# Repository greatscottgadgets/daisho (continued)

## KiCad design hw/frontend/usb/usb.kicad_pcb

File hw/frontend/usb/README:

Copyright (c) 2014 Jared Boone, ShareBrained Technology, Inc.

These files are part of Daisho.

License
=======

This is a free hardware design; you can redistribute it and/or modify
it under the terms of the GNU General Public License as published by
the Free Software Foundation; either version 2, or (at your option)
any later version.

This design is distributed in the hope that it will be useful,
but WITHOUT ANY WARRANTY; without even the implied warranty of
MERCHANTABILITY or FITNESS FOR A PARTICULAR PURPOSE.  See the
GNU General Public License for more details.

You should have received a copy of the GNU General Public License
along with this design; see the file COPYING.  If not, write to
the Free Software Foundation, Inc., 51 Franklin Street,
Boston, MA 02110-1301, USA.

Hardware Notes
==============

Schematic and layout files were designed in KiCad (release 2014-09-15
bzr 5135 -product), an open source electronic design automation package.

Order and type of copper layers:
    1_top: signal, front ("component" side, where most components are mounted)
    2: ground plane
    3: signal
    4: signal
    5: ground plane
    6_bot: signal, back (a few components mounted, mostly small passives)

PCB description:

    6 layer PCB, 62 mil +/- 5% thickness, using 8 layer construction

    LPI mask          0.4 mil
    Plating           1.2 mil   1.0 oz
    Copper      1     0.7 mil   0.5 oz
    Dielectric  1-2   4.4 mil   prepreg, 2 x 106-FR4 370
    Copper      2     1.2 mil   1.0 oz
    Dielectric  2-3   6.0 mil   core, FR4 370
    Copper      3     1.2 mil   1.0 oz
    Dielectric  3-4   8.1 mil   prepreg, 3 x 1080-FR4 370
                3-4  14.5 mil   core, FR4 370
                3-4   8.1 mil   prepreg, 3 x 1080-FR4 370
    Copper      4     1.2 mil   1.0 oz
    Dielectric  4-5   6.0 mil   core, FR4 370
    Copper      5     1.2 mil   1.0 oz
    Dielectric  5-6   4.4 mil   prepreg, 2 x 106-FR4 370
    Copper      6     0.7 mil   0.5 oz
    Plating           1.2 mil   1.0 oz
    LPI mask          0.4 mil

Impedance Goals
===============

50 Ohm +/- 10% microstrip, layers 1:2 and 6:5 at 0.178 mm (7.0 mil) width

50 Ohm +/- 10% offset stripline, layers 3:2 and 4:5 at 0.165 mm (6.5 mil) width

90 Ohm +/- 10% differential microstrip, layers 1:2 and 6:5 at 0.127 mm (5.0 mil) width, 0.127 mm (5.0 mil) separation

Soldermask
==========

Double side solder mask green
    +/- 5 mil solder mask registration

Silkscreen
==========

Double side silkscreen white
    6 mil silkscreen minimum width
    Silkscreen must be clipped by soldermask

Traces
======

5 mil (0.127 mm) min trace width
5 mil (0.127 mm) min trace isolation

Vias
====

8 mil (0.2032 mm) min via drill
17.7 mil (0.45 mm) min via pad
    4.85 mil min annular ring

Via-in-pad used in many places

Vias in pads need to be filled for assembly
    Most (all?) vias in pads are in capacitor footprints near the two 175-BGAs

Drills
======

Drills are specified in two files:
    usb_drill.xln contains plated drills.
    usb_drill_npth.xln contains non-plated drills.

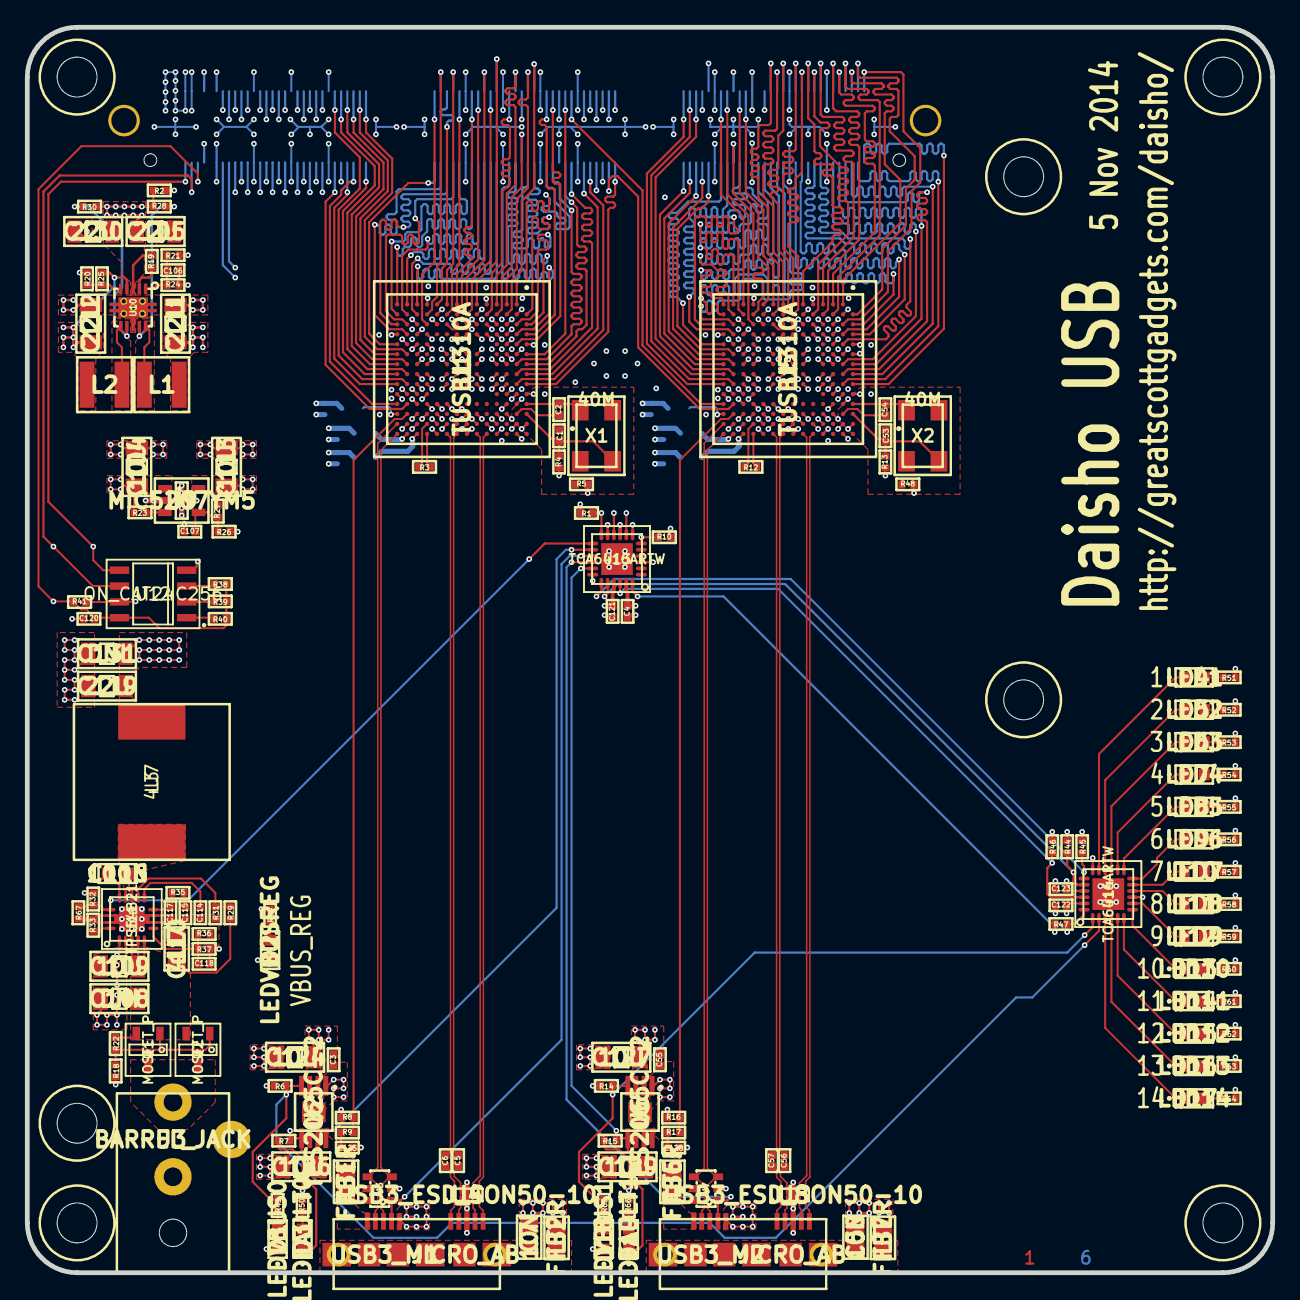
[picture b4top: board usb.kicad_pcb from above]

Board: 6 copper layers, 100.0 x 100.0 mm, 261 parts (0 on the bottom side), 265 nets.

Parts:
C1, C2, C53, C54: 27P; IPC_CAPC1005X55N
C3, C4, C5, C6, C8, C9, C10, C11, C12, C13, C14, C15, C16, C17, C18, C19, C20, C21, C22, C23, C24, C25, C26, C27, C28, C29, C30, C31, C32, C33, C34, C35, C36, C37, C38, C40, C41, C42, C43, C44, C45, C46, C47, C48, C49, C50, C51, C52, C55, C56, C57, C59, C60, C61, C62, C63, C64, C65, C66, C67, C68, C69, C70, C71, C72, C73, C74, C75, C76, C77, C78, C79, C80, C81, C82, C83, C84, C85, C86, C87, C88, C89, C91, C92, C93, C94, C95, C96, C97, C98, C99, C100, C101, C102, C103, C120, C121, C122, C123, C125, C128: 100N; IPC_CAPC1005X55N
C7, C58: 10N; IPC_CAPC2012X140N
C39, C90: 1U; IPC_CAPC1005X55N
C104, C109, C113, C124, C126, C127, C129: 10U; IPC_CAPC3216X180N
C105, C111, C112, C119, C130: 22U; IPC_CAPC3216X180N
C106: 33P; IPC_CAPC1005X55N
C107: 470P; IPC_CAPC1005X55N
C108, C131: DNI; IPC_CAPC3216X180N
C110: 4U7; IPC_CAPC2012X140N
C114: 22N; IPC_CAPC1005X55N
C115: 82N; IPC_CAPC1005X55N
C116: 100N; IPC_CAPC1608X90N
C117: 1N5; IPC_CAPC1005X55N
C118: 220P; IPC_CAPC1005X55N
D1: LEDVBUS0; IPC_LEDC1608X60N
D2: LEDVBUSREG; IPC_LEDC1608X60N
D3: LEDFAULT0; IPC_LEDC1608X60N
D4: LED1; IPC_LEDC1608X60N
D5: LED2; IPC_LEDC1608X60N
D6: LED3; IPC_LEDC1608X60N
D7: LED4; IPC_LEDC1608X60N
D8: LED5; IPC_LEDC1608X60N
D9: LED6; IPC_LEDC1608X60N
D10: LED7; IPC_LEDC1608X60N
D11: LED8; IPC_LEDC1608X60N
D12: LED9; IPC_LEDC1608X60N
D13: LED10; IPC_LEDC1608X60N
D14: LED11; IPC_LEDC1608X60N
D15: LED12; IPC_LEDC1608X60N
D16: LED13; IPC_LEDC1608X60N
D17: LED14; IPC_LEDC1608X60N
D18: LEDVBUS1; IPC_LEDC1608X60N
D19: LEDFAULT1; IPC_LEDC1608X60N
FB1, FB2, FB3, FB4, FB5, FB6, FB7, FB8, FB9, FB10: FILTER; IPC_INDC2012X130N
H1, H2, H4, H5, H6, H7, H8: HOLE; GSG-HOLE126MIL
J1, J2: USB3_MICRO_AB
J3: BARREL_JACK; CUI_PJ-102[AB]H
J4: SAMTEC_QSH-090-D; SAMTEC_QSH-090-01-F-D-A
L1, L2: 4U7; GSG-NRG4026
L3: 4U7; BOURNS_SRR1260
P4, P5, P6, P7, P8: CONN_1; GSG-TESTPOINT-50MIL
Q1, Q2: MOSFET_P; IPC_SOT95P280X125-3N_GSD
R1, R2, R3, R6, R7, R8, R10, R12, R14, R15, R16, R19, R44, R45, R46, R47: 10K; IPC_RESC1005X40N
R4, R5, R13, R38, R39, R40, R41, R48: DNI; IPC_RESC1005X40N
R9, R17: 90K9; IPC_RESC1005X40N
R18, R22: 30K; IPC_RESC1005X40N
R20: 165K; IPC_RESC1005X40N
R21: 180K; IPC_RESC1005X40N
R23, R28, R30: 0R; IPC_RESC1005X40N
R24: 360K; IPC_RESC1005X40N
R25: 137K; IPC_RESC1005X40N
R26: 174K; IPC_RESC1005X40N
R27: 105K; IPC_RESC1005X40N
R29: 22K; IPC_RESC1005X40N
R31: 9K53; IPC_RESC1005X40N
R32: 49K9; IPC_RESC1005X40N
R33: 52K3; IPC_RESC1005X40N
R34, R49, R50, R51, R52, R53, R54, R55, R56, R57, R58, R59, R60, R61, R62, R63, R64, R65, R66: 1K; IPC_RESC1005X40N
R35: 1K58; IPC_RESC1005X40N
R36: 2K21; IPC_RESC1005X40N
R37: 16K2; IPC_RESC1005X40N
R67: 1M; IPC_RESC1005X40N
U1, U5: TUSB1310A; IPC_BGA175C80P14X14_1200X1200X140
U2, U6: TPS2065C-2; TI_DGN_S-PDSO-G8
U3, U7: GSG-IP4220CZ6; GSG-SOT457
U4, U8: USB3_ESD_SON50-10
U9: MIC5207YM5; IPC_SOT95P280X110-5N
U10: TPS62420; TI_DRC_S-PVSON-N10
U11: TPS54821; TI_RHL_S-PVQFN-N14
U12: ON_CAT24C256; IPC_SOIC127P600X175-8N
U13, U14: TCA6416ARTW; ti_rtw_s-pwqfn-n24
X1, X2: 40M; IPC_OSCCC320X500X105-4N

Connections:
/main_board_if/EEPROM_A0: R40.1, U12.1
/main_board_if/EEPROM_A1: R39.1, U12.2
/main_board_if/EEPROM_A2: R38.1, U12.3
/main_board_if/EEPROM_VCC: C120.1, J4.6, P8.1, R38.2, R39.2, R40.2, R41.2, U12.8
/main_board_if/EEPROM_WP: P7.1, R41.1, U12.7
/main_board_if/FE_I2C_SCL: J4.4, P6.1, U12.6
/main_board_if/FE_I2C_SDA: J4.2, P5.1, U12.5
/main_board_if/IO_INT#: J4.14, R46.1, U13.22, U14.22
/main_board_if/IO_RESET#: J4.16, R47.2, U13.24, U14.24
/main_board_if/IO_SCL: J4.13, R45.1, U13.19, U14.19
/main_board_if/IO_SDA: J4.15, R44.1, U13.20, U14.20
/main_board_if/USB0_POWER_EN: R6.2, R49.2, U2.4, U14.2
/main_board_if/USB0_POWER_FLT#: D3.2, R7.2, U2.5, U13.14
/main_board_if/USB0_XI: J4.8, R4.2
/main_board_if/USB1_POWER_EN: R14.2, R65.2, U6.4, U14.1
/main_board_if/USB1_POWER_FLT#: D19.2, R15.2, U6.5, U13.17
/main_board_if/USB1_XI: J4.7, R13.2
/main_board_if/VALT_FE_PWRGD: R32.2, R67.2, U11.14, U13.13
/power/DC_IN: J3.1, Q1.D, Q2.D
/power/SW_PH: C116.2, L3.2, U11.11, U11.12
/power/SW_PVIN: C108.1, C109.1, C110.1, Q1.S, Q2.S, R22.2, R29.1, U11.4, U11.5, U11.6
/power/V1P1_FB: R20.1, R25.2, U10.5
/power/V1P1_SW: L2.1, U10.6
/power/V1P8_FB: C106.1, R21.1, R24.2, U10.1
/power/V1P8_SW: L1.2, U10.10
/usb0_interfaces/DM: J1.2, U1.P13, U3.4
/usb0_interfaces/DP: J1.3, U1.P14, U3.3
/usb0_interfaces/ELAS_BUF_MODE: J4.31, U1.C9
/usb0_interfaces/ID: J1.4, U3.1, U13.15
/usb0_interfaces/PCLK: J4.103, U1.A6
/usb0_interfaces/PHY_RESETN: U1.J3, U13.10
/usb0_interfaces/PHY_STATUS: J4.42, U1.E3
/usb0_interfaces/POWER_DOWN0: J4.46, U1.H3
/usb0_interfaces/POWER_DOWN1: J4.52, U1.G3
/usb0_interfaces/PWRPRESENT: J4.32, U1.H11
/usb0_interfaces/RESETN: R1.2, U1.J11, U13.12
/usb0_interfaces/RX_DATA0: J4.85, U1.E2
/usb0_interfaces/RX_DATA1: J4.90, U1.D2
/usb0_interfaces/RX_DATA2: J4.87, U1.D1
/usb0_interfaces/RX_DATA3: J4.91, U1.C1
/usb0_interfaces/RX_DATA4: J4.93, U1.C2
/usb0_interfaces/RX_DATA5: J4.98, U1.B1
/usb0_interfaces/RX_DATA6: J4.94, U1.A2
/usb0_interfaces/RX_DATA7: J4.88, U1.A3
/usb0_interfaces/RX_DATA8: J4.92, U1.B3
/usb0_interfaces/RX_DATA9: J4.97, U1.A4
/usb0_interfaces/RX_DATA10: J4.86, U1.B4
/usb0_interfaces/RX_DATA11: J4.99, U1.B5
/usb0_interfaces/RX_DATA12: J4.106, U1.B8
/usb0_interfaces/RX_DATA13: J4.110, U1.A8
/usb0_interfaces/RX_DATA14: J4.120, U1.A9
/usb0_interfaces/RX_DATA15: J4.112, U1.B9
/usb0_interfaces/RX_DATAK0: J4.104, U1.A7
/usb0_interfaces/RX_DATAK1: J4.100, U1.B7
/usb0_interfaces/RX_ELECIDLE: J4.17, U1.F3
/usb0_interfaces/RX_POLARITY: J4.29, U1.C8
/usb0_interfaces/RX_STATUS0: J4.21, U1.C5
/usb0_interfaces/RX_STATUS1: J4.25, U1.C6
/usb0_interfaces/RX_STATUS2: J4.27, U1.C7
/usb0_interfaces/RX_TERMINATION: J4.19, U1.D3
/usb0_interfaces/RX_VALID: J4.81, U1.F1
/usb0_interfaces/SSRXM: J1.9, U1.F14, U4.4
/usb0_interfaces/SSRXP: J1.10, U1.E14, U4.5
/usb0_interfaces/SSTXM: C6.1, U1.J14
/usb0_interfaces/SSTXM_C: C6.2, J1.6, U4.1
/usb0_interfaces/SSTXP: C5.1, U1.H14
/usb0_interfaces/SSTXP_C: C5.2, J1.7, U4.2
/usb0_interfaces/TX_CLK: J4.65, U1.K1
/usb0_interfaces/TX_DATA0: J4.62, U1.P5
/usb0_interfaces/TX_DATA1: J4.64, U1.N4
/usb0_interfaces/TX_DATA2: J4.66, U1.P3
/usb0_interfaces/TX_DATA3: J4.68, U1.N3
/usb0_interfaces/TX_DATA4: J4.70, U1.P2
/usb0_interfaces/TX_DATA5: J4.76, U1.N2
/usb0_interfaces/TX_DATA6: J4.74, U1.P1
/usb0_interfaces/TX_DATA7: J4.78, U1.N1
/usb0_interfaces/TX_DATA8: J4.82, U1.M1
/usb0_interfaces/TX_DATA9: J4.80, U1.M2
/usb0_interfaces/TX_DATA10: J4.63, U1.L2
/usb0_interfaces/TX_DATA11: J4.61, U1.L3
/usb0_interfaces/TX_DATA12: J4.69, U1.J2
/usb0_interfaces/TX_DATA13: J4.73, U1.H1
/usb0_interfaces/TX_DATA14: J4.75, U1.H2
/usb0_interfaces/TX_DATA15: J4.79, U1.G2
/usb0_interfaces/TX_DATAK0: J4.67, U1.J1
/usb0_interfaces/TX_DATAK1: J4.77, U1.G1
/usb0_interfaces/TX_DEEMPH0: J4.28, U1.L11
/usb0_interfaces/TX_DEEMPH1: J4.30, U1.K11
/usb0_interfaces/TX_DETRX_LPBK: J4.38, U1.M6
/usb0_interfaces/TX_ELECIDLE: J4.44, U1.K3
/usb0_interfaces/TX_MARGIN0: J4.22, U1.M9
/usb0_interfaces/TX_MARGIN1: J4.20, U1.M10
/usb0_interfaces/TX_MARGIN2: J4.18, U1.M11
/usb0_interfaces/TX_ONESZEROS: U1.M4, U13.11
/usb0_interfaces/TX_SWING: J4.40, U1.M5
/usb0_interfaces/ULPI_CLK: J4.56, U1.P11
/usb0_interfaces/ULPI_DATA0: J4.49, U1.N9
/usb0_interfaces/ULPI_DATA1: J4.54, U1.P9
/usb0_interfaces/ULPI_DATA2: J4.60, U1.P8
/usb0_interfaces/ULPI_DATA3: J4.51, U1.N8
/usb0_interfaces/ULPI_DATA4: J4.53, U1.P7
/usb0_interfaces/ULPI_DATA5: J4.55, U1.N7
/usb0_interfaces/ULPI_DATA6: J4.57, U1.P6
/usb0_interfaces/ULPI_DATA7: J4.59, U1.N6
/usb0_interfaces/ULPI_DIR: J4.34, U1.M7
/usb0_interfaces/ULPI_NXT: J4.50, U1.N11
/usb0_interfaces/ULPI_STP: J4.26, U1.M8
/usb0_interfaces/USB3_SHIELD: C7.1, FB2.2, J1.11
/usb0_interfaces/VBUS: C125.1, C126.1, FB1.1, R9.2, U2.6, U2.7, U2.8
/usb0_interfaces/VBUS_RAW: FB1.2, J1.1, U3.5
/usb0_interfaces/VSSOSC: C1.2, C2.2, R5.2, U1.B12, X1.2, X1.4
/usb0_interfaces/XI: C1.1, R4.1, U1.A12, X1.3
/usb0_interfaces/XO: C2.1, U1.A11, X1.1
/usb0_power/A1P1: C39.1, C45.1, C47.1, C49.1, C50.1, C51.1, C52.1, FB5.2, U1.C11, U1.C12, U1.D14, U1.G13, U1.G14, U1.K14, U1.M14
/usb0_power/A1P8: C44.1, C46.1, C48.1, FB4.2, U1.A13, U1.C10, U1.N14
/usb0_power/A3P3: C43.1, FB3.2, U1.P12
/usb1_interfaces/DM: J2.2, U5.P13, U7.4
/usb1_interfaces/DP: J2.3, U5.P14, U7.3
/usb1_interfaces/ELAS_BUF_MODE: J4.137, U5.C9
/usb1_interfaces/ID: J2.4, U7.1, U13.16
/usb1_interfaces/PCLK: J4.147, U5.A6
/usb1_interfaces/PHY_RESETN: U5.J3, U13.7
/usb1_interfaces/PHY_STATUS: J4.101, U5.E3
/usb1_interfaces/POWER_DOWN0: J4.111, U5.H3
/usb1_interfaces/POWER_DOWN1: J4.113, U5.G3
/usb1_interfaces/PWRPRESENT: J4.114, U5.H11
/usb1_interfaces/RESETN: R10.2, U5.J11, U13.6
/usb1_interfaces/RX_DATA0: J4.163, U5.E2
/usb1_interfaces/RX_DATA1: J4.169, U5.D2
/usb1_interfaces/RX_DATA2: J4.165, U5.D1
/usb1_interfaces/RX_DATA3: J4.171, U5.C1
/usb1_interfaces/RX_DATA4: J4.173, U5.C2
/usb1_interfaces/RX_DATA5: J4.175, U5.B1
/usb1_interfaces/RX_DATA6: J4.177, U5.A2
/usb1_interfaces/RX_DATA7: J4.158, U5.A3
/usb1_interfaces/RX_DATA8: J4.179, U5.B3
/usb1_interfaces/RX_DATA9: J4.164, U5.A4
/usb1_interfaces/RX_DATA10: J4.160, U5.B4
/usb1_interfaces/RX_DATA11: J4.166, U5.B5
/usb1_interfaces/RX_DATA12: J4.174, U5.B8
/usb1_interfaces/RX_DATA13: J4.176, U5.A8
/usb1_interfaces/RX_DATA14: J4.180, U5.A9
/usb1_interfaces/RX_DATA15: J4.178, U5.B9
/usb1_interfaces/RX_DATAK0: J4.172, U5.A7
/usb1_interfaces/RX_DATAK1: J4.170, U5.B7
/usb1_interfaces/RX_ELECIDLE: J4.115, U5.F3
/usb1_interfaces/RX_POLARITY: J4.129, U5.C8
/usb1_interfaces/RX_STATUS0: J4.119, U5.C5
/usb1_interfaces/RX_STATUS1: J4.127, U5.C6
/usb1_interfaces/RX_STATUS2: J4.162, U5.C7
/usb1_interfaces/RX_TERMINATION: J4.117, U5.D3
/usb1_interfaces/RX_VALID: J4.161, U5.F1
/usb1_interfaces/SSRXM: J2.9, U5.F14, U8.4
/usb1_interfaces/SSRXP: J2.10, U5.E14, U8.5
/usb1_interfaces/SSTXM: C57.1, U5.J14
/usb1_interfaces/SSTXM_C: C57.2, J2.6, U8.1
/usb1_interfaces/SSTXP: C56.1, U5.H14
/usb1_interfaces/SSTXP_C: C56.2, J2.7, U8.2
/usb1_interfaces/TX_CLK: J4.139, U5.K1
/usb1_interfaces/TX_DATA0: J4.134, U5.P5
/usb1_interfaces/TX_DATA1: J4.136, U5.N4
/usb1_interfaces/TX_DATA2: J4.140, U5.P3
/usb1_interfaces/TX_DATA3: J4.154, U5.N3
/usb1_interfaces/TX_DATA4: J4.152, U5.P2
/usb1_interfaces/TX_DATA5: J4.148, U5.N2
/usb1_interfaces/TX_DATA6: J4.150, U5.P1
/usb1_interfaces/TX_DATA7: J4.146, U5.N1
/usb1_interfaces/TX_DATA8: J4.133, U5.M1
/usb1_interfaces/TX_DATA9: J4.142, U5.M2
/usb1_interfaces/TX_DATA10: J4.138, U5.L2
/usb1_interfaces/TX_DATA11: J4.135, U5.L3
/usb1_interfaces/TX_DATA12: J4.149, U5.J2
/usb1_interfaces/TX_DATA13: J4.151, U5.H1
/usb1_interfaces/TX_DATA14: J4.153, U5.H2
/usb1_interfaces/TX_DATA15: J4.159, U5.G2
/usb1_interfaces/TX_DATAK0: J4.141, U5.J1
/usb1_interfaces/TX_DATAK1: J4.157, U5.G1
/usb1_interfaces/TX_DEEMPH0: J4.37, U5.L11
/usb1_interfaces/TX_DEEMPH1: J4.33, U5.K11
/usb1_interfaces/TX_DETRX_LPBK: J4.89, U5.M6
/usb1_interfaces/TX_ELECIDLE: J4.109, U5.K3
/usb1_interfaces/TX_MARGIN0: J4.41, U5.M9
/usb1_interfaces/TX_MARGIN1: J4.43, U5.M10
/usb1_interfaces/TX_MARGIN2: J4.45, U5.M11
/usb1_interfaces/TX_ONESZEROS: U5.M4, U13.8
/usb1_interfaces/TX_SWING: J4.102, U5.M5
/usb1_interfaces/ULPI_CLK: J4.105, U5.P11
/usb1_interfaces/ULPI_DATA0: J4.123, U5.N9
/usb1_interfaces/ULPI_DATA1: J4.121, U5.P9
/usb1_interfaces/ULPI_DATA2: J4.125, U5.P8
/usb1_interfaces/ULPI_DATA3: J4.122, U5.N8
/usb1_interfaces/ULPI_DATA4: J4.124, U5.P7
/usb1_interfaces/ULPI_DATA5: J4.126, U5.N7
/usb1_interfaces/ULPI_DATA6: J4.128, U5.P6
/usb1_interfaces/ULPI_DATA7: J4.130, U5.N6
/usb1_interfaces/ULPI_DIR: J4.116, U5.M7
/usb1_interfaces/ULPI_NXT: J4.118, U5.N11
/usb1_interfaces/ULPI_STP: J4.39, U5.M8
/usb1_interfaces/USB3_SHIELD: C58.1, FB7.2, J2.11
/usb1_interfaces/VBUS: C128.1, C129.1, FB6.1, R17.2, U6.6, U6.7, U6.8
/usb1_interfaces/VBUS_RAW: FB6.2, J2.1, U7.5
/usb1_interfaces/VSSOSC: C53.2, C54.2, R48.2, U5.B12, X2.2, X2.4
/usb1_interfaces/XI: C53.1, R13.1, U5.A12, X2.3
/usb1_interfaces/XO: C54.1, U5.A11, X2.1
/usb1_power/A1P1: C90.1, C96.1, C98.1, C100.1, C101.1, C102.1, C103.1, FB10.2, U5.C11, U5.C12, U5.D14, U5.G13, U5.G14, U5.K14, U5.M14
/usb1_power/A1P8: C95.1, C97.1, C99.1, FB9.2, U5.A13, U5.C10, U5.N14
/usb1_power/A3P3: C94.1, FB8.2, U5.P12
GND: C3.2, C4.2, C7.2, C8.2, C9.2, C10.2, C11.2, C12.2, C13.2, C14.2, C15.2, C16.2, C17.2, C18.2, C19.2, C20.2, C21.2, C22.2, C23.2, C24.2, C25.2, C26.2, C27.2, C28.2, C29.2, C30.2, C31.2, C32.2, C33.2, C34.2, C35.2, C36.2, C37.2, C38.2, C39.2, C40.2, C41.2, C42.2, C43.2, C44.2, C45.2, C46.2, C47.2, C48.2, C49.2, C50.2, C51.2, C52.2, C55.2, C58.2, C59.2, C60.2, C61.2, C62.2, C63.2, C64.2, C65.2, C66.2, C67.2, C68.2, C69.2, C70.2, C71.2, C72.2, C73.2, C74.2, C75.2, C76.2, C77.2, C78.2, C79.2, C80.2, C81.2, C82.2, C83.2, C84.2, C85.2, C86.2, C87.2, C88.2, C89.2, C90.2, C91.2, C92.2, C93.2, C94.2, C95.2, C96.2, C97.2, C98.2, C99.2, C100.2, C101.2, C102.2, C103.2, C104.2, C105.2, C107.2, C108.2, C109.2, C110.2, C111.2, C112.1, C113.2, C114.2, C115.2, C117.2, C119.2, C120.2, C121.2, C122.2, C123.2, C124.2, C125.2, C126.2, C127.2, C128.2, C129.2, C130.2, C131.2, D1.2, D2.2, D18.2, FB2.1, FB7.1, J1.5, J1.8, J2.5, J2.8, J3.2, J4.A0, J4.A1, J4.A2, J4.A3, J4.B0, J4.B1, J4.B2, J4.B3, J4.C0, J4.C1, J4.C2, J4.C3, P4.1, R1.1, R5.1, R6.1, R8.2, R10.1, R14.1, R16.2, R18.1, R20.2, R21.2, R26.2, R31.1, R33.1, R36.1, R47.1, R48.1, R67.1, U1.B11, U1.B13, U1.B14, U1.D12, U1.E13, U1.F6, U1.F7, U1.F8, U1.F9, U1.F12, U1.F13, U1.G6, U1.G7, U1.G8, U1.G9, U1.G12, U1.H6, U1.H7, U1.H8, U1.H9, U1.H13, U1.J6, U1.J7, U1.J8, U1.J9, U1.J13, U1.K12, U1.L12, U1.M12, U1.M13, U1.N13, U2.1, U2.9, U3.2, U4.3, U5.B11, U5.B13, U5.B14, U5.D12, U5.E13, U5.F6, U5.F7, U5.F8, U5.F9, U5.F12, U5.F13, U5.G6, U5.G7, U5.G8, U5.G9, U5.G12, U5.H6, U5.H7, U5.H8, U5.H9, U5.H13, U5.J6, U5.J7, U5.J8, U5.J9, U5.J13, U5.K12, U5.L12, U5.M12, U5.M13, U5.N13, U6.1, U6.9, U7.2, U8.3, U9.2, U10.0, U10.8, U11.2, U11.3, U11.15, U12.4, U13.9, U13.18, U13.25, U14.9, U14.25
unnamed: C107.1, R26.1, R27.2, U9.4
unnamed: C114.1, U11.9
unnamed: C115.1, R35.1
unnamed: C116.1, U11.13
unnamed: C117.1, R35.2, U11.8
unnamed: C118.2, R36.2, R37.1, U11.7
unnamed: D1.1, R49.1
unnamed: D2.1, R34.1
unnamed: D3.1, R50.2
unnamed: D4.1, R51.1
unnamed: D4.2, U14.17
unnamed: D5.1, R52.1
unnamed: D5.2, U14.16
unnamed: D6.1, R53.1
unnamed: D6.2, U14.15
unnamed: D7.1, R54.1
unnamed: D7.2, U14.14
unnamed: D8.1, R55.1
unnamed: D8.2, U14.13
unnamed: D9.1, R56.1
unnamed: D9.2, U14.12
unnamed: D10.1, R57.1
unnamed: D10.2, U14.11
unnamed: D11.1, R58.1
unnamed: D11.2, U14.10
unnamed: D12.1, R59.1
unnamed: D12.2, U14.8
unnamed: D13.1, R60.1
unnamed: D13.2, U14.7
unnamed: D14.1, R61.1
unnamed: D14.2, U14.6
unnamed: D15.1, R62.1
unnamed: D15.2, U14.5
unnamed: D16.1, R63.1
unnamed: D16.2, U14.4
unnamed: D17.1, R64.1
unnamed: D17.2, U14.3
unnamed: D18.1, R65.1
unnamed: D19.1, R66.2
unnamed: Q1.G, Q2.G, R18.2, R22.1
unnamed: R3.1, U1.L13
unnamed: R3.2, U1.L14
unnamed: R8.1, R9.1, U1.N12
unnamed: R12.1, U5.L13
unnamed: R12.2, U5.L14
unnamed: R16.1, R17.1, U5.N12
unnamed: R19.2, U10.2
unnamed: R23.2, U9.3
unnamed: R28.1, U10.9
unnamed: R29.2, R31.2, U11.10
unnamed: R30.1, U10.7
unnamed: R33.2, U11.1
V1P1: C9.1, C11.1, C13.1, C15.1, C17.1, C19.1, C21.1, C23.1, C25.1, C27.1, C29.1, C31.1, C33.1, C35.1, C37.1, C42.1, C60.1, C62.1, C64.1, C66.1, C68.1, C70.1, C72.1, C74.1, C76.1, C78.1, C80.1, C82.1, C84.1, C86.1, C88.1, C93.1, C112.2, FB5.1, FB10.1, L2.2, R25.1, U1.A5, U1.A10, U1.B6, U1.B10, U1.C4, U1.D13, U1.E1, U1.F2, U1.K2, U1.K13, U1.L1, U1.N5, U1.N10, U1.P4, U1.P10, U5.A5, U5.A10, U5.B6, U5.B10, U5.C4, U5.D13, U5.E1, U5.F2, U5.K2, U5.K13, U5.L1, U5.N5, U5.N10, U5.P4, U5.P10, U10.4
V1P8: C4.1, C8.1, C10.1, C12.1, C14.1, C16.1, C18.1, C20.1, C22.1, C24.1, C26.1, C28.1, C30.1, C32.1, C34.1, C36.1, C38.1, C41.1, C59.1, C61.1, C63.1, C65.1, C67.1, C69.1, C71.1, C73.1, C75.1, C77.1, C79.1, C81.1, C83.1, C85.1, C87.1, C89.1, C92.1, C106.2, C111.1, C121.1, C122.1, FB4.1, FB9.1, J4.12, J4.24, J4.36, J4.48, J4.71, J4.72, J4.83, J4.84, J4.95, J4.96, J4.107, J4.108, J4.131, J4.132, J4.143, J4.144, J4.155, J4.156, J4.167, J4.168, L1.1, R24.1, R44.2, R45.2, R46.2, U1.B2, U1.C3, U1.D4, U1.D7, U1.D8, U1.D9, U1.E4, U1.F4, U1.G4, U1.H4, U1.L4, U1.L5, U1.L7, U1.L8, U1.L9, U1.L10, U1.M3, U5.B2, U5.C3, U5.D4, U5.D7, U5.D8, U5.D9, U5.E4, U5.F4, U5.G4, U5.H4, U5.L4, U5.L5, U5.L7, U5.L8, U5.L9, U5.L10, U5.M3, U13.21, U13.23, U14.23
V3P3D: C40.1, C91.1, C113.1, FB3.1, FB8.1, R27.1, U9.5
VBUS_REG: C3.1, C55.1, C118.1, C119.1, C124.1, C127.1, C131.1, J4.1, J4.3, L3.1, R2.2, R34.2, R37.2, U2.2, U2.3, U6.2, U6.3, U13.3
VRAW_SW: C104.1, C105.1, C123.1, C130.1, J4.11, J4.23, J4.35, J4.47, R2.1, R7.1, R15.1, R19.1, R23.1, R28.2, R30.2, R32.1, R50.1, R51.2, R52.2, R53.2, R54.2, R55.2, R56.2, R57.2, R58.2, R59.2, R60.2, R61.2, R62.2, R63.2, R64.2, R66.1, U9.1, U10.3, U14.18, U14.21

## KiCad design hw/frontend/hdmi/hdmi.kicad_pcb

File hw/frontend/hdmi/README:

Copyright (c) 2014 Michael Ossmann, Mike Kershaw, Jared Boone

These files are part of Daisho.

License
=======

This is a free hardware design; you can redistribute it and/or modify
it under the terms of the GNU General Public License as published by
the Free Software Foundation; either version 2, or (at your option)
any later version.

This design is distributed in the hope that it will be useful,
but WITHOUT ANY WARRANTY; without even the implied warranty of
MERCHANTABILITY or FITNESS FOR A PARTICULAR PURPOSE.  See the
GNU General Public License for more details.

You should have received a copy of the GNU General Public License
along with this design; see the file COPYING.  If not, write to
the Free Software Foundation, Inc., 51 Franklin Street,
Boston, MA 02110-1301, USA.

Hardware Notes
==============

Schematic and layout files were designed in KiCad (release 2014-10-14
bzr 5188 -product), an open source electronic design automation package.

Order and type of copper layers:
    C1F: signal, front ("component" side, where most components are mounted)
    C2: ground plane
    C3: signal
    C4: signal
    C5: ground plane
    C6B: signal, back (a few components mounted, mostly small passives)

PCB description:

    6 layer PCB, 62 mil +/- 5% thickness, using 8 layer construction

    LPI mask          0.4 mil
    Plating           1.2 mil   1.0 oz
    Copper      1     0.7 mil   0.5 oz
    Dielectric  1-2   4.4 mil   prepreg, 2 x 106-FR4 370
    Copper      2     1.2 mil   1.0 oz
    Dielectric  2-3   6.0 mil   core, FR4 370
    Copper      3     1.2 mil   1.0 oz
    Dielectric  3-4   8.1 mil   prepreg, 3 x 1080-FR4 370
                3-4  14.5 mil   core, FR4 370
                3-4   8.1 mil   prepreg, 3 x 1080-FR4 370
    Copper      4     1.2 mil   1.0 oz
    Dielectric  4-5   6.0 mil   core, FR4 370
    Copper      5     1.2 mil   1.0 oz
    Dielectric  5-6   4.4 mil   prepreg, 2 x 106-FR4 370
    Copper      6     0.7 mil   0.5 oz
    Plating           1.2 mil   1.0 oz
    LPI mask          0.4 mil

Impedance Goals
===============

50 Ohm +/- 10% microstrip, layers 1:2 and 6:5 at 0.178 mm (7.0 mil) width

100 Ohm +/- 10% differential microstrip, layers 1:2 and 6:5 at 0.127 mm (5.0 mil) width, 0.127 mm (8.0 mil) separation

Soldermask
==========

Double side solder mask green
    +/- 5 mil solder mask registration

Silkscreen
==========

Double side silkscreen white
    6 mil silkscreen minimum width
    Silkscreen must be clipped by soldermask

Traces
======

5 mil (0.127 mm) min trace width
5 mil (0.127 mm) min trace isolation

Vias
====

8 mil (0.2032 mm) min via drill
17.7 mil (0.45 mm) min via pad
    4.85 mil min annular ring

Via-in-pad used in many places

Vias in pads need to be filled for assembly
    All vias in pads are in capacitor footprints near the BGA

Drills
======

Drills are specified in two files:
    hdmi.drl contains plated drills.
    hdmi-NPTH.drl contains non-plated drills.

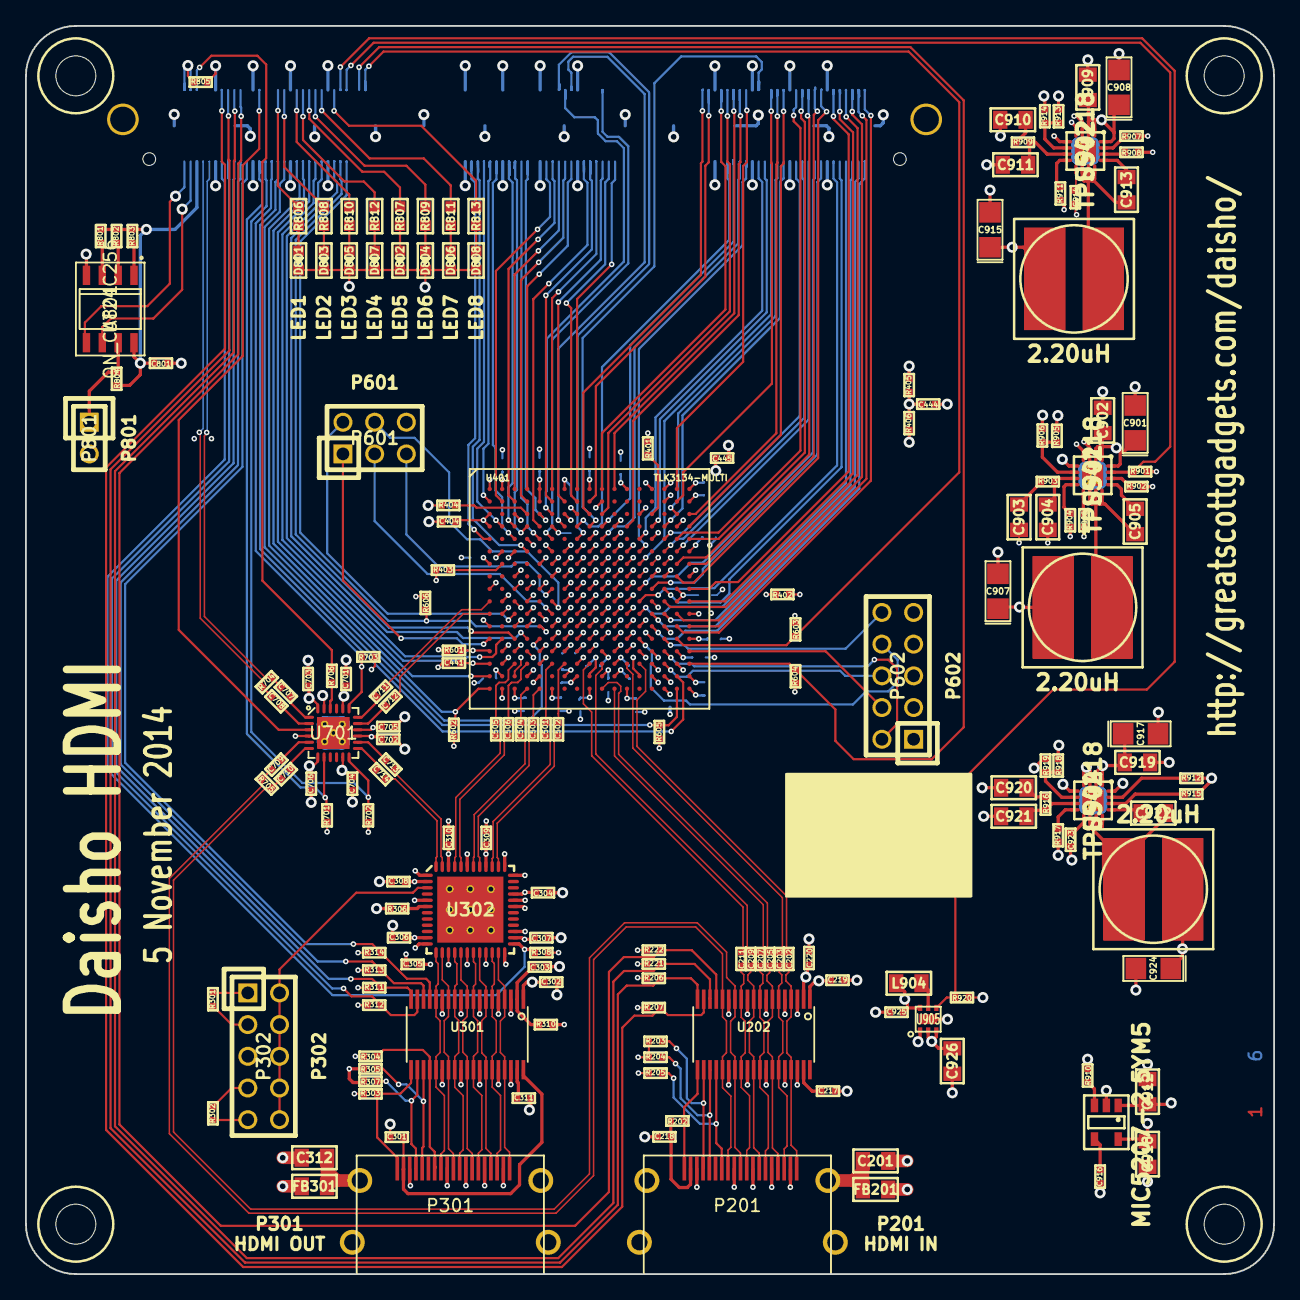
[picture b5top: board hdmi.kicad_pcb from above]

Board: 6 copper layers, 100.0 x 100.0 mm, 228 parts (0 on the bottom side), 237 nets.

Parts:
C201, C312: DNP; GSG-0805
C202, C203, C205, C207, C209, C211, C218, C219, C220, C301, C302, C303, C501, C502, C503, C504, C505, C506, C701, C702, C703, C704, C705, C706, C707, C708, C709, C710, C711, C712, C713, C714, C801: 0.1uF; GSG-0402
C217, C311: 0.1uF 10V; GSG-0402
C304, C305, C306, C307, C308, C309, C310, C407, C409, C411, C414, C416, C417, C419, C421, C422, C423, C424, C425, C426, C434, C436, C437, C439, C442, C443, C445, C447, C448, C449, C450, C451: 0.01uF; GSG-0402
C401, C402, C404, C925: 2.2uF; GSG-0402
C403, C406, C408, C418, C433, C444: 1uF; GSG-0402
C405, C410, C412, C420, C432, C435: 0.47uF; GSG-0402
C413, C427, C428, C440: 100pF; GSG-0402
C415, C429, C430, C431, C438, C441: 10pF; GSG-0402
C901, C907, C908, C915, C917, C924: 22uF; gsg-sm1206p
C902, C905, C909, C913, C919, C922: 100nF; GSG-0805
C903, C920: 27nF; GSG-0805
C904, C921: 82pF; GSG-0805
C906, C914, C923: 12nF; GSG-0402
C910: 22nF; GSG-0805
C911: 100pF; GSG-0805
C912, C918, C926: 10uF; GSG-0805
C916: 470pF; GSG-0402
D801: LED1; GSG-0603D
D802: LED5; GSG-0603D
D803: LED2; GSG-0603D
D804: LED6; GSG-0603D
D805: LED3; GSG-0603D
D806: LED7; GSG-0603D
D807: LED4; GSG-0603D
D808: LED8; GSG-0603D
FB201, FB301: FILTER; GSG-0805
H1, H2, H3, H4: HOLE; GSG-HOLE126MIL
J801: SAMTEC_QSH-090-D; SAMTEC_QSH-090-01-F-D-A
L901, L902, L903: 2.20uH; TDK_VLP8040
L904: 1uH; GSG-0805
P201, P301: HDMI; 10029449-111RLF
P302, P602: CONN_02X05; GSG-HEADER-2x5
P601: CONN_02X03; GSG-HEADER-2x3
P801: CONN_01X02; GSG-HEADER-1x2
R202: 1k; GSG-0402
R203, R204, R207, R221, R222, R312, R313, R314: 47k; GSG-0402
R205, R304: 27k; GSG-0402
R206, R311: 100k; GSG-0402
R301, R302, R303, R308, R310, R601, R602, R603, R604, R805, R901, R902, R907, R908, R910, R912, R915, R920: 10k; GSG-0402
R305, R307: 1k8; GSG-0402
R306: 10k 1%; GSG-0402
R401, R402, R405, R406: 150 0.5%; GSG-0402
R403, R404: 50 0.5%; GSG-0402
R605, R606, R701, R702, R703: 1.5k; GSG-0402
R704, R705: 100; GSG-0402
R706: 20; GSG-0402
R801, R802, R803, R804: DNP; GSG-0402
R806, R807, R808, R809, R810, R811, R812, R813: 180; GSG-0603
R903, R916: 2.87k; GSG-0402
R904, R911, R917: 158k 1%; GSG-0402
R905: 210k 1%; GSG-0402
R906, R914: 105k 1%; GSG-0402
R909: 3.24k; GSG-0402
R913, R919: 120k 1%; GSG-0402
R918: 38.3k 1%; GSG-0402
U202: TPD12S520; GSG-TSSOP38
U301: TPD12S521; GSG-TSSOP38
U302: PTN3360DBS; QFN48-7
U401: TLK3134-MULTI; PBGA-289
U701: SI5338B; GSG-QFN24
U801: ON_CAT24C256; IPC_SOIC127P600X175-8N
U901, U902, U904: TPS54218; TI_RTE_S-PWQFN-N16
U903: MIC5207-2.5YM5; IPC_SOT95P280X110-5N
U905: FAN4860UMP; ULMP-6

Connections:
/HDMI Input/IN_SHELL: C201.1, FB201.1, P201.20
/HDMI Output/HDMI_OUT_CK_M_SHIFTED: P301.12, U301.15, U301.24, U302.13
/HDMI Output/HDMI_OUT_CK_P_SHIFTED: P301.10, U301.13, U301.26, U302.14
/HDMI Output/HDMI_OUT_D0_M_SHIFTED: P301.9, U301.12, U301.27, U302.16
/HDMI Output/HDMI_OUT_D0_P_SHIFTED: P301.7, U301.10, U301.29, U302.17
/HDMI Output/HDMI_OUT_D1_M_SHIFTED: P301.6, U301.9, U301.30, U302.19
/HDMI Output/HDMI_OUT_D1_P_SHIFTED: P301.4, U301.7, U301.32, U302.20
/HDMI Output/HDMI_OUT_D2_M_SHIFTED: P301.3, U301.6, U301.33, U302.22
/HDMI Output/HDMI_OUT_D2_P_SHIFTED: P301.1, U301.4, U301.35, U302.23
/HDMI Output/OUT_SHELL: C312.1, FB301.1, P301.20
/Mezzanine/EEPROM_A0: R803.2, U801.1
/Mezzanine/EEPROM_A1: R802.2, U801.2
/Mezzanine/EEPROM_A2: R801.2, U801.3
/Mezzanine/EEPROM_WP: P801.1, R804.2, U801.7
/Mezzanine/FE_I2C_SCL: J801.4, U801.6
/Mezzanine/FE_I2C_SDA: J801.2, U801.5
/Mezzanine/FE_I2C_VCC: C801.1, J801.6, R801.1, R802.1, R803.1, R804.1, U801.8
/Mezzanine/LED1: J801.31, R806.1
/Mezzanine/LED2: J801.33, R808.1
/Mezzanine/LED3: J801.37, R810.1
/Mezzanine/LED4: J801.39, R812.1
/Mezzanine/LED5: J801.41, R807.1
/Mezzanine/LED6: J801.43, R809.1
/Mezzanine/LED7: J801.45, R811.1
/Mezzanine/LED8: J801.49, R813.1
/Mezzanine/VALT_FE: J801.1, J801.3, R805.2
/Serdes Power/VREF: C444.1, C445.1, R405.2, R406.1, U401.A14, U401.H14
CEC_IN_SUPP: J801.19, R222.1, U202.16
CLK_HDMI_OUT_M: C714.1, U302.48
CLK_HDMI_OUT_P: C713.1, U302.47
CLK_IN_M_SUPP: C709.2, P201.12, R705.1, U202.15, U202.24
CLK_IN_P_SUPP: C710.2, P201.10, R705.2, U202.13, U202.26
DATA0_IN_M_SUPP: C211.1, P201.9, U202.12, U202.27
DATA0_IN_P_SUPP: C209.1, P201.7, U202.10, U202.29
DATA1_IN_M_SUPP: C207.1, P201.6, U202.9, U202.30
DATA1_IN_P_SUPP: C205.1, P201.4, U202.7, U202.32
DATA2_IN_M_SUPP: C203.1, P201.3, U202.6, U202.33
DATA2_IN_P_SUPP: C202.1, P201.1, U202.4, U202.35
FE_CLKSRC: J801.5, R706.1
FE_CLK_AUX: J801.25, U701.3
FE_CLK_N0: C707.2, J801.10, R704.1
FE_CLK_P0: C708.2, J801.8, R704.2
GND: C201.2, C217.1, C218.2, C219.1, C220.2, C301.2, C302.1, C303.2, C304.2, C305.2, C306.2, C307.2, C308.2, C309.2, C310.2, C311.1, C312.2, C401.2, C402.2, C403.2, C404.2, C405.2, C406.2, C407.2, C408.2, C409.2, C410.2, C411.2, C412.2, C413.2, C414.2, C415.2, C416.2, C417.2, C418.2, C419.2, C420.2, C421.2, C422.2, C423.2, C424.2, C425.2, C426.2, C427.2, C428.2, C429.2, C430.2, C431.2, C432.2, C433.2, C434.2, C435.2, C436.2, C437.2, C438.2, C439.2, C440.2, C441.2, C442.2, C443.2, C444.2, C445.2, C447.2, C448.2, C449.2, C450.2, C451.2, C701.1, C702.2, C703.2, C704.2, C705.2, C706.2, C801.2, C901.2, C902.2, C903.2, C904.2, C906.1, C907.2, C908.2, C909.2, C910.2, C911.2, C912.2, C914.1, C915.2, C916.2, C917.2, C918.2, C919.2, C920.2, C921.2, C923.1, C924.2, C925.2, C926.2, D801.2, D802.2, D803.2, D804.2, D805.2, D806.2, D807.2, D808.2, FB201.2, FB301.2, J801.A0, J801.A1, J801.A2, J801.A3, J801.B0, J801.B1, J801.B2, J801.B3, J801.C0, J801.C1, J801.C2, J801.C3, P201.2, P201.5, P201.8, P201.11, P201.17, P301.2, P301.5, P301.8, P301.11, P301.17, P302.1, P601.6, P602.3, P602.5, P602.9, P801.2, R301.1, R303.2, R306.1, R401.2, R402.2, R403.2, R404.2, R406.2, R601.2, R602.2, R603.2, R604.2, R901.1, R904.2, R905.1, R911.2, R913.1, R917.2, R918.2, R920.2, U202.3, U202.5, U202.8, U202.11, U202.14, U202.25, U202.28, U202.31, U202.34, U202.36, U301.3, U301.5, U301.8, U301.11, U301.14, U301.25, U301.28, U301.31, U301.34, U301.36, U302.0, U302.1, U302.5, U302.12, U302.18, U302.24, U302.27, U302.31, U302.32, U302.36, U302.37, U302.43, U401.A1, U401.A7, U401.A17, U401.B10, U401.C3, U401.C13, U401.D6, U401.D16, U401.E9, U401.F2, U401.F12, U401.G5, U401.G7, U401.G8, U401.G9, U401.G10, U401.G11, U401.G15, U401.H7, U401.H8, U401.H9, U401.H10, U401.H11, U401.H12, U401.J1, U401.J3, U401.J4, U401.J8, U401.J9, U401.J10, U401.J11, U401.K3, U401.K4, U401.K7, U401.K8, U401.K9, U401.K10, U401.K11, U401.K12, U401.K14, U401.L5, U401.L7, U401.L8, U401.L9, U401.L10, U401.L11, U401.L17, U401.M3, U401.M4, U401.M6, U401.M7, U401.M8, U401.M9, U401.M10, U401.M11, U401.M13, U401.P2, U401.P4, U401.P5, U401.P6, U401.P8, U401.P10, U401.P12, U401.P13, U401.R2, U401.T3, U401.T5, U401.T8, U401.T11, U401.T14, U401.T15, U401.U2, U401.U17, U701.0, U701.4, U701.23, U801.4, U901.3, U901.4, U901.5, U901.17, U902.3, U902.4, U902.5, U902.17, U903.2, U904.3, U904.4, U904.5, U904.17, U905.0, U905.1
HDMI_CEC_OUT: J801.22, R314.1, U301.16
HDMI_HPD_OUT: J801.18, R311.1, U301.19
HDMI_OUT_EN: J801.14, R308.2, U302.25
HDMI_SCL_OUT: J801.20, R313.1, U301.17
HDMI_SDA_OUT: J801.16, R312.1, U301.18
HPD_IN_SUPP: J801.15, R206.1, U202.19
unnamed: C217.2, U202.37
unnamed: C218.1, P201.18, R202.1
unnamed: C301.1, P301.18, U301.38
unnamed: C303.1, R310.2, U301.2
unnamed: C311.2, U301.37
unnamed: C501.1, U401.R6
unnamed: C502.1, U401.R7
unnamed: C503.1, U401.U5
unnamed: C504.1, U401.U4
unnamed: C505.1, U401.R3
unnamed: C506.1, U401.R4
unnamed: C707.1, U701.1
unnamed: C708.1, U701.2
unnamed: C709.1, U701.5
unnamed: C710.1, U701.6
unnamed: C711.2, U701.18
unnamed: C712.2, U701.17
unnamed: C713.2, U701.14
unnamed: C714.2, U701.13
unnamed: C903.1, R903.2
unnamed: C904.1, R903.1, U901.7
unnamed: C905.1, U901.13
unnamed: C905.2, L901.1, U901.10, U901.11, U901.12
unnamed: C906.2, U901.9
unnamed: C910.1, R909.2
unnamed: C911.1, R909.1, U902.7
unnamed: C913.1, U902.13
unnamed: C913.2, L902.1, U902.10, U902.11, U902.12
unnamed: C914.2, U902.9
unnamed: C916.1, U903.4
unnamed: C920.1, R916.2
unnamed: C921.1, R916.1, U904.7
unnamed: C922.1, U904.13
unnamed: C922.2, L903.1, U904.10, U904.11, U904.12
unnamed: C923.2, U904.9
unnamed: D801.1, R806.2
unnamed: D802.1, R807.2
unnamed: D803.1, R808.2
unnamed: D804.1, R809.2
unnamed: D805.1, R810.2
unnamed: D806.1, R811.2
unnamed: D807.1, R812.2
unnamed: D808.1, R813.2
unnamed: L904.1, U905.5
unnamed: P201.13, R205.1, U202.23
unnamed: P201.15, R204.1, U202.22
unnamed: P201.16, R203.1, U202.21
unnamed: P201.19, R202.2, U202.20
unnamed: P301.13, R304.2, U301.23
unnamed: P301.15, R305.2, U301.22
unnamed: P301.16, R307.2, U301.21
unnamed: P301.19, R303.1, U301.20
unnamed: P302.3, R301.2
unnamed: P302.9, R302.2
unnamed: P302.2, P302.4, P302.6, P302.8, P302.10, U302.3
unnamed: R306.2, U302.6
unnamed: R401.1, U401.C14
unnamed: R402.1, U401.H15
unnamed: R403.1, U401.G2
unnamed: R404.1, U401.C4
unnamed: R706.2, U701.22
unnamed: R902.2, U901.14
unnamed: R904.1, U901.8
unnamed: R905.2, R906.2, U901.6
unnamed: R907.1, U902.15
unnamed: R908.1, U902.14
unnamed: R910.1, U903.3
unnamed: R911.1, U902.8
unnamed: R912.2, U904.15
unnamed: R913.2, R914.2, U902.6
unnamed: R915.2, U904.14
unnamed: R917.1, U904.8
unnamed: R918.1, R919.1, U904.6
SCL_IN_SUPP: J801.17, R221.1, U202.17
SDA_IN_SUPP: J801.13, R207.1, U202.18
SD_CH0_RX0: J801.140, U401.E10
SD_CH0_RX1: J801.138, U401.D10
SD_CH0_RX2: J801.137, U401.A11
SD_CH0_RX3: J801.127, U401.C9
SD_CH0_RX4: J801.133, U401.A10
SD_CH0_RX5: J801.129, U401.B9
SD_CH0_RX6: J801.136, U401.D8
SD_CH0_RX7: J801.118, U401.B8
SD_CH0_RX8: J801.135, U401.C10
SD_CH0_RX9: J801.110, U401.D5
SD_CH0_RXCLK: J801.145, U401.D9
SD_CH0_TX0: J801.179, U401.M16
SD_CH0_TX1: J801.178, U401.L14
SD_CH0_TX2: J801.174, U401.L13
SD_CH0_TX3: J801.175, U401.L16
SD_CH0_TX4: J801.177, U401.M17
SD_CH0_TX5: J801.173, U401.K15
SD_CH0_TX6: J801.169, U401.J17
SD_CH0_TX7: J801.172, U401.J15
SD_CH0_TX8: J801.176, U401.L15
SD_CH0_TX9: J801.151, U401.C17
SD_CH0_TXCLK: J801.180, U401.M14
SD_CH1_RX0: J801.120, U401.A8
SD_CH1_RX1: J801.114, U401.A6
SD_CH1_RX2: J801.112, U401.B6
SD_CH1_RX3: J801.106, U401.A4
SD_CH1_RX4: J801.104, U401.B4
SD_CH1_RX5: J801.92, U401.C5
SD_CH1_RX6: J801.100, U401.B3
SD_CH1_RX7: J801.102, U401.A3
SD_CH1_RX8: J801.101, U401.E8
SD_CH1_RX9: J801.86, U401.D3
SD_CH1_RXCLK: J801.105, U401.D7
SD_CH1_TX0: J801.166, U401.J14
SD_CH1_TX1: J801.164, U401.J13
SD_CH1_TX2: J801.163, U401.G17
SD_CH1_TX3: J801.150, U401.G13
SD_CH1_TX4: J801.161, U401.G16
SD_CH1_TX5: J801.160, U401.F15
SD_CH1_TX6: J801.159, U401.E17
SD_CH1_TX7: J801.157, U401.E16
SD_CH1_TX8: J801.171, U401.K17
SD_CH1_TX9: J801.141, U401.A16
SD_CH1_TXCLK: J801.170, U401.K13
SD_CH2_RX0: J801.115, U401.E6
SD_CH2_RX1: J801.98, U401.B2
SD_CH2_RX2: J801.88, U401.D4
SD_CH2_RX3: J801.80, U401.B1
SD_CH2_RX4: J801.90, U401.E5
SD_CH2_RX5: J801.78, U401.D2
SD_CH2_RX6: J801.82, U401.E3
SD_CH2_RX7: J801.74, U401.E1
SD_CH2_RX8: J801.116, U401.B7
SD_CH2_RX9: J801.76, U401.F4
SD_CH2_RXCLK: J801.103, U401.C6
SD_CH2_TX0: J801.158, U401.E15
SD_CH2_TX1: J801.153, U401.D17
SD_CH2_TX2: J801.152, U401.C16
SD_CH2_TX3: J801.142, U401.F13
SD_CH2_TX4: J801.154, U401.D15
SD_CH2_TX5: J801.149, U401.B16
SD_CH2_TX6: J801.146, U401.E13
SD_CH2_TX7: J801.148, U401.D14
SD_CH2_TX8: J801.165, U401.H16
SD_CH2_TX9: J801.139, U401.D12
SD_CH2_TXCLK: J801.162, U401.F16
SERDES_ENABLE: J801.40, R602.1, U401.U1
SERDES_GPO0: P601.1, U401.N1
SERDES_GPO1: P601.2, U401.L3
SERDES_GPO2: P601.3, U401.L6
SERDES_GPO3: P601.4, U401.K6
SERDES_GPO4: P601.5, U401.J6
SERDES_HDMI_IN0_M: C211.2, U401.R9
SERDES_HDMI_IN0_P: C209.2, U401.R10
SERDES_HDMI_IN1_M: C207.2, U401.U11
SERDES_HDMI_IN1_P: C205.2, U401.U10
SERDES_HDMI_IN2_M: C203.2, U401.R12
SERDES_HDMI_IN2_P: C202.2, U401.R13
SERDES_HDMI_OUT0_M: C506.2, U302.44
SERDES_HDMI_OUT0_P: C505.2, U302.45
SERDES_HDMI_OUT1_M: C504.2, U302.42
SERDES_HDMI_OUT1_P: C503.2, U302.41
SERDES_HDMI_OUT2_M: C502.2, U302.38
SERDES_HDMI_OUT2_P: C501.2, U302.39
SERDES_MDC: J801.32, U401.T16
SERDES_MDIO_ST: J801.54, R606.1, U401.M5
SERDES_MDO: J801.34, R605.1, U401.U16
SERDES_PLOOP: J801.59, R603.1, U401.N16
SERDES_PRTAD0: J801.42, U401.T1
SERDES_PRTAD1: J801.44, U401.N2
SERDES_PRTAD2: J801.52, U401.N3
SERDES_PRTAD3: J801.50, U401.N4
SERDES_PRTAD4: J801.38, U401.N5
SERDES_REFCLK_M: C711.1, U401.K1
SERDES_REFCLK_P: C712.1, U401.L1
SERDES_RST_N: J801.46, R601.1, U401.P1
SERDES_SLOOP: J801.57, R604.1, U401.R17
SERDES_TCK: P602.4, U401.P17
SERDES_TDI: P602.8, U401.N13
SERDES_TDO: P602.6, U401.R15
SERDES_TMS: P602.2, U401.P15
SERDES_TRST_N: P602.10, U401.N15
SI5338_INTR: J801.26, R701.1, U701.8
SI5338_SCL: J801.28, R702.2, U701.12
SI5338_SDA: J801.30, R703.1, U701.19
V1P2_EN: J801.53, R901.2, U901.15
V1P2_REGULATED: C401.1, C403.1, C405.1, C407.1, C409.1, C411.1, C413.1, C415.1, C418.1, C420.1, C422.1, C424.1, C426.1, C428.1, C430.1, C432.1, C434.1, C436.1, C438.1, C442.1, C443.1, C447.1, C448.1, C449.1, C450.1, C451.1, C907.1, L901.2, R906.1, U401.D11, U401.E11, U401.F6, U401.F8, U401.F9, U401.F11, U401.G6, U401.G12, U401.J5, U401.J7, U401.J12, U401.K2, U401.L4, U401.M1, U401.M12, U401.N6, U401.N7, U401.N8, U401.N10, U401.N11, U401.N12, U401.N17, U401.P7, U401.P11, U401.R5, U401.R8, U401.R11, U401.R14, U401.T2, U401.T4, U401.T7, U401.T9, U401.T10, U401.T13, U401.U3, U401.U6, U401.U9, U401.U12, U401.U15
V1P5_REGULATED: C402.1, C404.1, C406.1, C408.1, C410.1, C412.1, C414.1, C416.1, C417.1, C419.1, C421.1, C423.1, C425.1, C427.1, C429.1, C431.1, C915.1, J801.71, J801.72, J801.83, J801.84, J801.95, J801.96, J801.107, J801.108, J801.131, J801.132, J801.143, J801.144, J801.155, J801.156, J801.167, J801.168, L902.2, R405.1, R914.1, U401.A2, U401.A5, U401.A9, U401.A12, U401.A15, U401.B5, U401.B15, U401.B17, U401.C1, U401.C7, U401.C8, U401.D1, U401.E4, U401.E14, U401.F3, U401.F7, U401.F10, U401.F17, U401.G1, U401.G14, U401.H3, U401.H6, U401.H13, U401.H17, U401.J16, U401.K16, U401.L12, U401.M15, U401.P9
V2P5_REGULATED: C220.1, C433.1, C435.1, C437.1, C439.1, C440.1, C441.1, C702.1, C703.1, C704.1, C705.1, C706.1, C918.1, J801.12, J801.24, J801.36, J801.48, P602.1, R206.2, R207.2, R221.2, R222.2, R310.1, R311.2, R312.2, R313.2, R314.2, R605.2, R606.2, R701.2, R702.1, R703.2, U202.2, U401.L2, U401.N9, U401.N14, U401.P3, U401.P14, U401.P16, U401.R1, U401.R16, U401.T17, U701.7, U701.11, U701.15, U701.16, U701.24, U903.5
V3P3_REGULATED: C304.1, C305.1, C306.1, C307.1, C308.1, C309.1, C310.1, C701.2, C912.1, C924.1, C925.1, L903.2, L904.2, P302.7, R205.2, R302.1, R304.1, R308.1, R910.2, R919.2, U302.2, U302.11, U302.15, U302.21, U302.26, U302.33, U302.40, U302.46, U701.20, U903.1, U905.6
V5P0_EN: J801.51, R920.1, U905.4
V5P0_REGULATED: C219.2, C302.2, C926.1, R203.2, R204.2, R305.1, R307.1, U202.1, U301.1, U905.2, U905.3
VRAW_SW: C901.1, C902.1, C908.1, C909.1, C917.1, C919.1, J801.11, J801.23, J801.35, J801.47, R805.1, R902.1, R907.2, R908.2, R912.1, R915.1, U901.1, U901.2, U901.16, U902.1, U902.2, U902.16, U904.1, U904.2, U904.16
